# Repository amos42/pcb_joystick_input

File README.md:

# Arcade Joystick 입력 장치

---

[74HC165를 사용한 Arcade Joystick 입력 보드 (DIP. 1P Ver.)](joystick_74hc165_input_1p/)
([README.md](joystick_74hc165_input_1p/README.md))

---

[74HC165를 사용한 Arcade Joystick 입력 보드 (DIP. 2P Ver.)](joystick_74hc165_input/)
([README.md](joystick_74hc165_input/README.md))

---

[74HC165를 사용한 Arcade Joystick 입력 보드 (SMD. 2P Ver.)](joystick_74hc165_input_smd/)
([README.md](joystick_74hc165_input_smd/README.md))

---

[74HC165를 사용한 Arcade Joystick 입력 보드 (JST 커넥터. 2P Ver)](joystick_74hc165_input_jst/)
([README.md](joystick_74hc165_input_jst/README.md))

---

[Raspberry Pie GPIO 입력 모듈](joystick_gpio_input/)
([README.md](joystick_gpio_input/README.md))

---

[Arcade 입력 패널 Support 보드](arcade_input_panel_support/)
([README.md](arcade_input_panel_support/README.md))

---

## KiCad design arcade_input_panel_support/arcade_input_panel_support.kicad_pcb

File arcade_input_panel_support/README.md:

# Arcade Input Panel Support Board

다음과 같은 수치에 맞춰 제작 된 입력 패널에서만 사용이 가능하다.

혹은 [도면 파일](input_panel.svg)을 받아서 종이에 프린트하여 나무판에 붙이고 직접 홀쏘로 구멍을 뚫어 사용해도 된다.

### 회로도

### PCB

### PCB 샘플 이미지

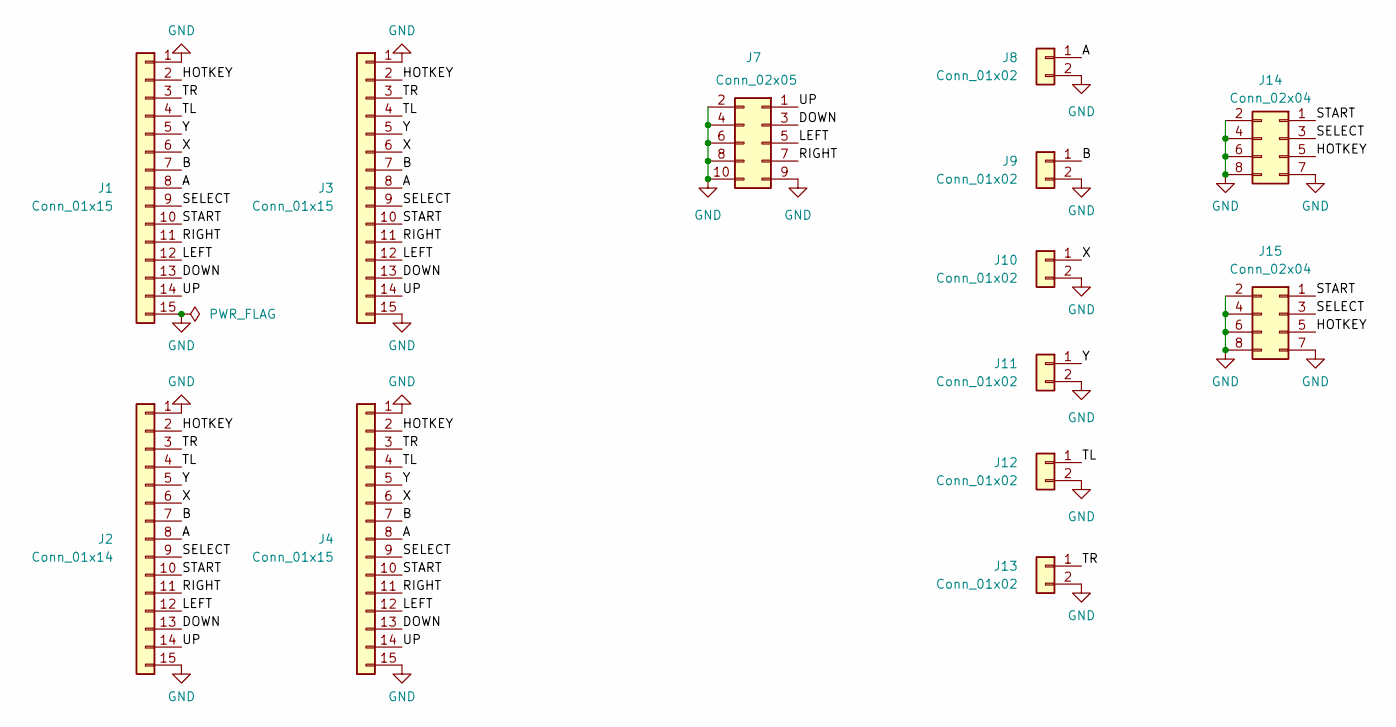
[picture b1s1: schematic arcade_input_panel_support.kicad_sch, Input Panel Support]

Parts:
J1: Conn_01x15; Molex_PicoBlade_53047-1510_1x15_P1.25mm_Vertical
J2: Conn_01x14; Molex_PicoBlade_53047-1510_1x15_P1.25mm_Vertical
J3, J4: Conn_01x15; PinHeader_1x15_P2.54mm_Vertical
J7: Conn_02x05; PinHeader_2x05_P2.54mm_Vertical
J8, J9, J10, J11, J12, J13: Conn_01x02; PinHeader_1x02_P2.54mm_Vertical
J14, J15: Conn_02x04; PinHeader_2x04_P2.54mm_Vertical

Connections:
/A: J1.8, J2.8, J3.8, J4.8, J8.1
/B: J1.7, J2.7, J3.7, J4.7, J9.1
/DOWN: J1.13, J2.13, J3.13, J4.13, J7.3
/HOTKEY: J1.2, J2.2, J3.2, J4.2, J14.5, J15.5
/LEFT: J1.12, J2.12, J3.12, J4.12, J7.5
/RIGHT: J1.11, J2.11, J3.11, J4.11, J7.7
/SELECT: J1.9, J2.9, J3.9, J4.9, J14.3, J15.3
/START: J1.10, J2.10, J3.10, J4.10, J14.1, J15.1
/TL: J1.4, J2.4, J3.4, J4.4, J12.1
/TR: J1.3, J2.3, J3.3, J4.3, J13.1
/UP: J1.14, J2.14, J3.14, J4.14, J7.1
/X: J1.6, J2.6, J3.6, J4.6, J10.1
/Y: J1.5, J2.5, J3.5, J4.5, J11.1
GND: J1.1, J1.15, J2.1, J2.15, J3.1, J3.15, J4.1, J4.15, J7.2, J7.4, J7.6, J7.8, J7.9, J7.10, J8.2, J9.2, J10.2, J11.2, J12.2, J13.2, J14.2, J14.4, J14.6, J14.7, J14.8, J15.2, J15.4, J15.6, J15.7, J15.8

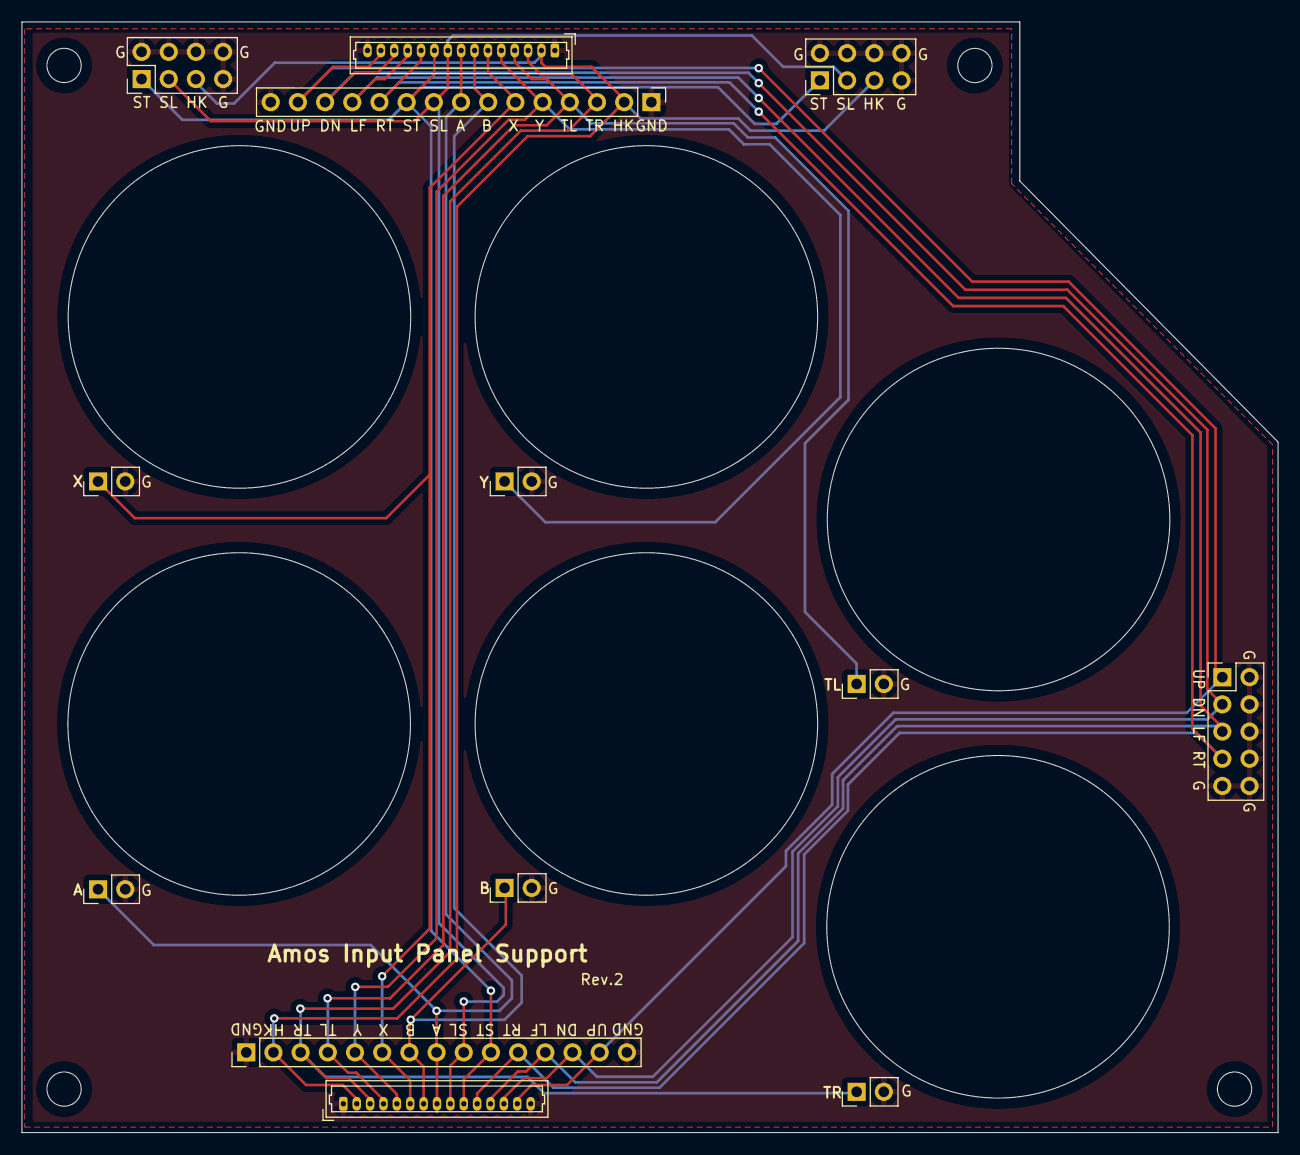
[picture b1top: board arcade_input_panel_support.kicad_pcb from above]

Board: 2 copper layers, 117.3 x 103.8 mm, 13 parts (0 on the bottom side), 14 nets.

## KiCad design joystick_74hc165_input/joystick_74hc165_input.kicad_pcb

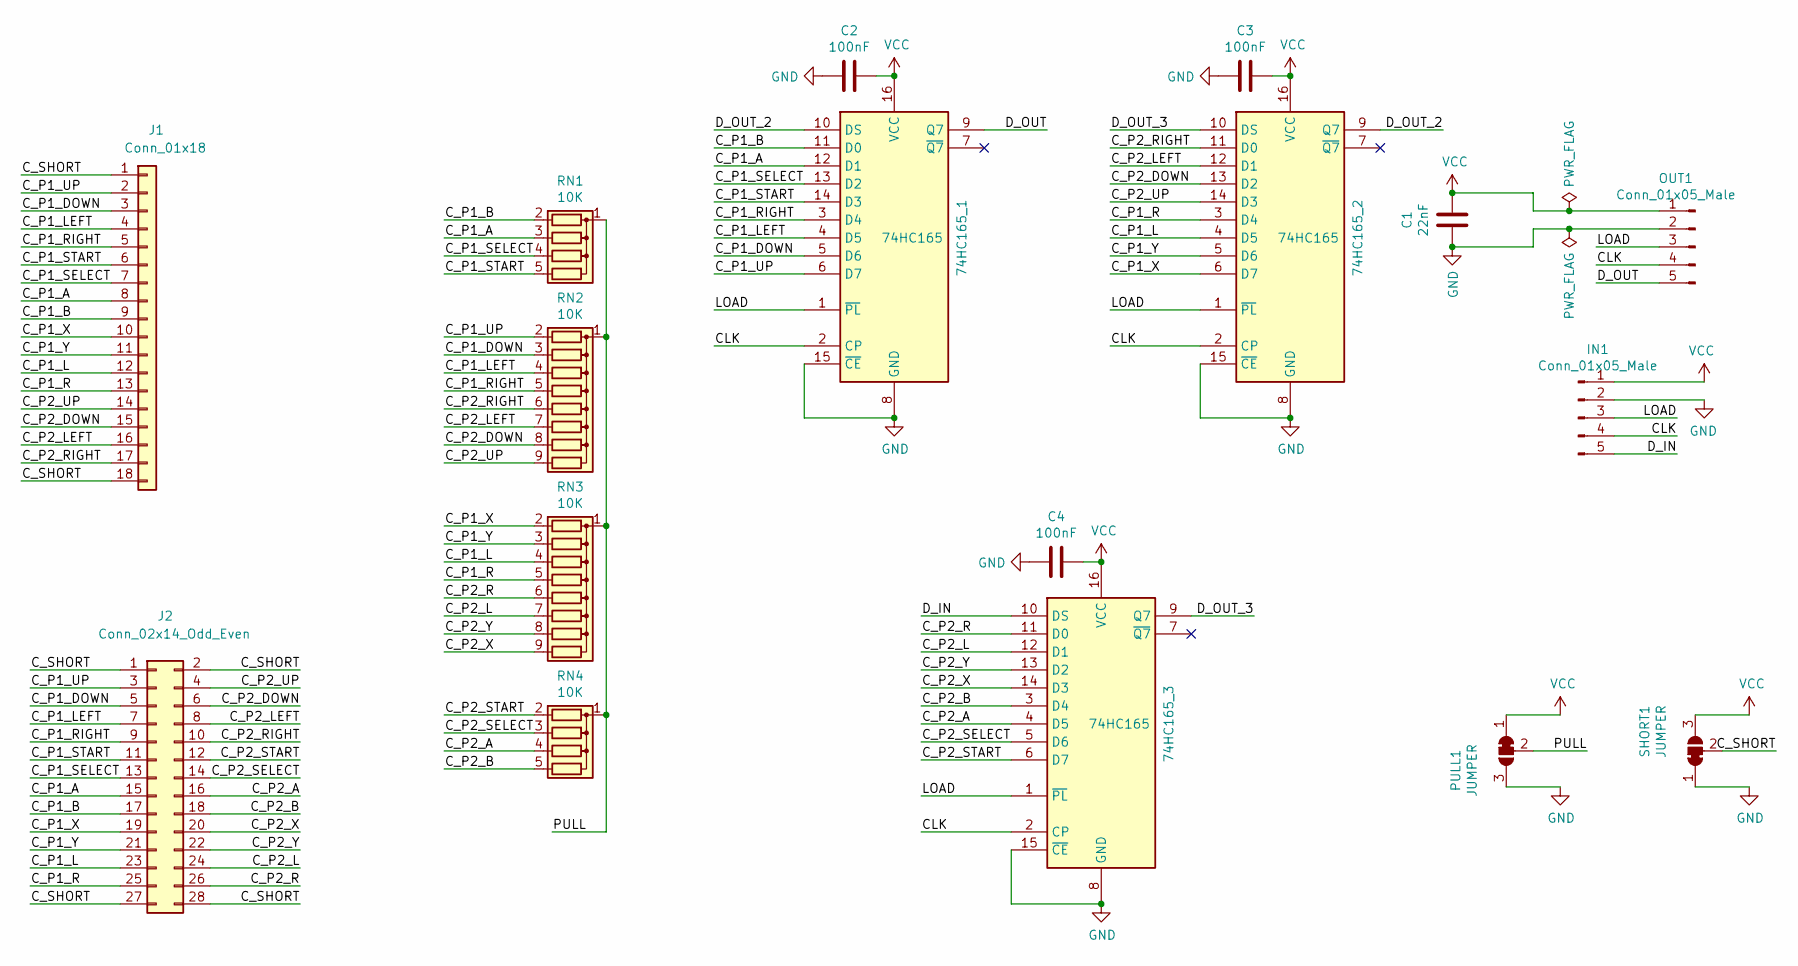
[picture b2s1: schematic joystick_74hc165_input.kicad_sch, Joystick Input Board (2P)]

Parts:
74HC165_1, 74HC165_2, 74HC165_3: 74HC165; DIP-16_W7.62mm
C1: 22nF; C_0805_2012Metric_Pad1.18x1.45mm_HandSolder
C2, C3, C4: 100nF; C_0805_2012Metric_Pad1.18x1.45mm_HandSolder
IN1: Conn_01x05_Male; PinHeader_1x05_P2.54mm_Vertical
J1: Conn_01x18; PinHeader_1x18_P2.54mm_Vertical
J2: Conn_02x14_Odd_Even; PinHeader_2x14_P2.54mm_Vertical
OUT1: Conn_01x05_Male; PinHeader_1x05_P2.54mm_Vertical
PULL1: JUMPER; SolderJumper-3_P1.3mm_Bridged12_Pad1.0x1.5mm_NumberLabels
RN1, RN4: 10K; R_Array_SIP5
RN2, RN3: 10K; R_Array_SIP9
SHORT1: JUMPER; SolderJumper-3_P1.3mm_Bridged12_Pad1.0x1.5mm_NumberLabels

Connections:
/CLK: 74HC165_1.2 (CP), 74HC165_2.2 (CP), 74HC165_3.2 (CP), IN1.4, OUT1.4
/C_P1_A: 74HC165_1.12 (D1), J1.8, J2.15, RN1.3 (R2)
/C_P1_B: 74HC165_1.11 (D0), J1.9, J2.17, RN1.2 (R1)
/C_P1_DOWN: 74HC165_1.5 (D6), J1.3, J2.5, RN2.3 (R2)
/C_P1_L: 74HC165_2.4 (D5), J1.12, J2.23, RN3.4 (R3)
/C_P1_LEFT: 74HC165_1.4 (D5), J1.4, J2.7, RN2.4 (R3)
/C_P1_R: 74HC165_2.3 (D4), J1.13, J2.25, RN3.5 (R4)
/C_P1_RIGHT: 74HC165_1.3 (D4), J1.5, J2.9, RN2.5 (R4)
/C_P1_SELECT: 74HC165_1.13 (D2), J1.7, J2.13, RN1.4 (R3)
/C_P1_START: 74HC165_1.14 (D3), J1.6, J2.11, RN1.5 (R4)
/C_P1_UP: 74HC165_1.6 (D7), J1.2, J2.3, RN2.2 (R1)
/C_P1_X: 74HC165_2.6 (D7), J1.10, J2.19, RN3.2 (R1)
/C_P1_Y: 74HC165_2.5 (D6), J1.11, J2.21, RN3.3 (R2)
/C_P2_A: 74HC165_3.4 (D5), J2.16, RN4.4 (R3)
/C_P2_B: 74HC165_3.3 (D4), J2.18, RN4.5 (R4)
/C_P2_DOWN: 74HC165_2.13 (D2), J1.15, J2.6, RN2.8 (R7)
/C_P2_L: 74HC165_3.12 (D1), J2.24, RN3.7 (R6)
/C_P2_LEFT: 74HC165_2.12 (D1), J1.16, J2.8, RN2.7 (R6)
/C_P2_R: 74HC165_3.11 (D0), J2.26, RN3.6 (R5)
/C_P2_RIGHT: 74HC165_2.11 (D0), J1.17, J2.10, RN2.6 (R5)
/C_P2_SELECT: 74HC165_3.5 (D6), J2.14, RN4.3 (R2)
/C_P2_START: 74HC165_3.6 (D7), J2.12, RN4.2 (R1)
/C_P2_UP: 74HC165_2.14 (D3), J1.14, J2.4, RN2.9 (R8)
/C_P2_X: 74HC165_3.14 (D3), J2.20, RN3.9 (R8)
/C_P2_Y: 74HC165_3.13 (D2), J2.22, RN3.8 (R7)
/C_SHORT: J1.1, J1.18, J2.1, J2.2, J2.27, J2.28, SHORT1.2 (C)
/D_IN: 74HC165_3.10 (DS), IN1.5
/D_OUT: 74HC165_1.9 (Q7), OUT1.5
/D_OUT_2: 74HC165_1.10 (DS), 74HC165_2.9 (Q7)
/D_OUT_3: 74HC165_2.10 (DS), 74HC165_3.9 (Q7)
/LOAD: 74HC165_1.1 (~PL), 74HC165_2.1 (~PL), 74HC165_3.1 (~PL), IN1.3, OUT1.3
/PULL: PULL1.2 (C), RN1.1 (common), RN2.1 (common), RN3.1 (common), RN4.1 (common)
GND: 74HC165_1.8 (GND), 74HC165_1.15 (~CE), 74HC165_2.8 (GND), 74HC165_2.15 (~CE), 74HC165_3.8 (GND), 74HC165_3.15 (~CE), C1.2, C2.2, C3.2, C4.2, IN1.2, OUT1.2, PULL1.3 (B), SHORT1.1 (A)
VCC: 74HC165_1.16 (VCC), 74HC165_2.16 (VCC), 74HC165_3.16 (VCC), C1.1, C2.1, C3.1, C4.1, IN1.1, OUT1.1, PULL1.1 (A), SHORT1.3 (B)

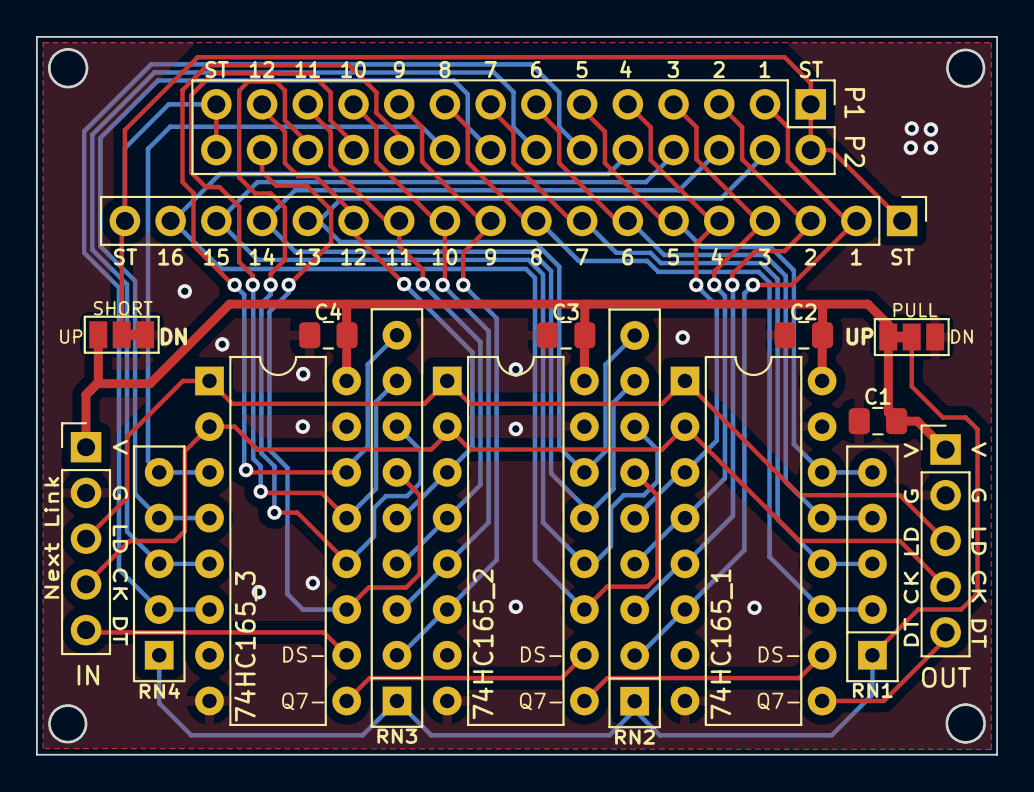
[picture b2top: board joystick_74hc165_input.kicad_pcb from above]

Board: 2 copper layers, 53.3 x 39.9 mm, 17 parts (0 on the bottom side), 34 nets.

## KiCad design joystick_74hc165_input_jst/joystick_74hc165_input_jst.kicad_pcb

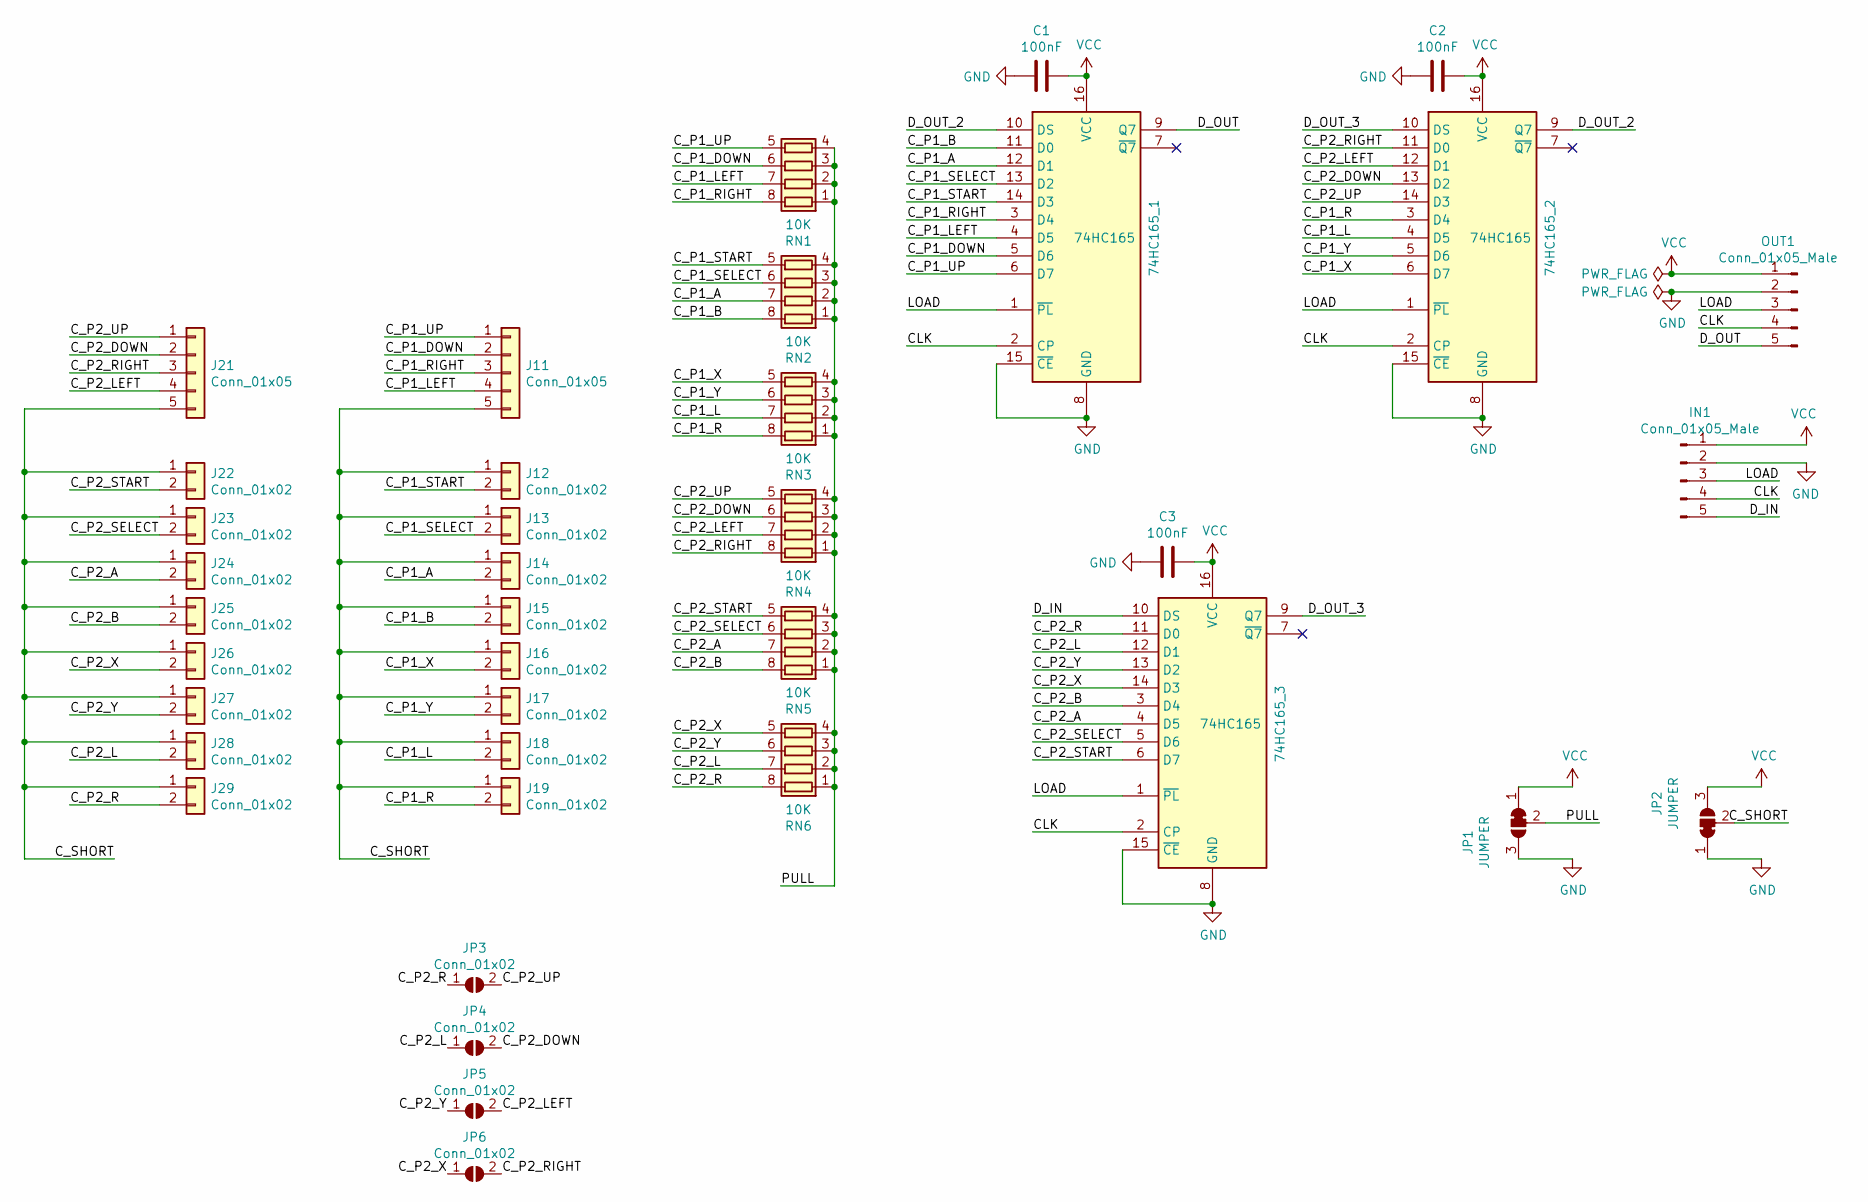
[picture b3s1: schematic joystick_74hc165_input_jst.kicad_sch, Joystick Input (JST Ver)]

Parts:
74HC165_1, 74HC165_2, 74HC165_3: 74HC165; SOIC-16_3.9x9.9mm_P1.27mm
C1, C2, C3: 100nF; C_0805_2012Metric_Pad1.18x1.45mm_HandSolder
IN1: Conn_01x05_Male; PinHeader_1x05_P2.54mm_Vertical
J11, J21: Conn_01x05; JST_XH_B5B-XH-A_1x05_P2.50mm_Vertical
J12, J13, J14, J15, J16, J17, J18, J19, J22, J23, J24, J25, J26, J27, J28, J29: Conn_01x02; JST_XH_B2B-XH-A_1x02_P2.50mm_Vertical
JP1, JP2: JUMPER; SolderJumper-3_P1.3mm_Bridged12_Pad1.0x1.5mm_NumberLabels
JP3, JP4, JP5, JP6: Conn_01x02; SolderJumper-2_P1.3mm_Bridged_RoundedPad1.0x1.5mm
OUT1: Conn_01x05_Male; PinHeader_1x05_P2.54mm_Vertical
RN1, RN2, RN3, RN4, RN5, RN6: 10K; R_Array_Concave_4x0603

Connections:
/CLK: 74HC165_1.2 (CP), 74HC165_2.2 (CP), 74HC165_3.2 (CP), IN1.4, OUT1.4
/C_P1_A: 74HC165_1.12 (D1), J14.2, RN2.7 (R2.2)
/C_P1_B: 74HC165_1.11 (D0), J15.2, RN2.8 (R1.2)
/C_P1_DOWN: 74HC165_1.5 (D6), J11.2, RN1.6 (R3.2)
/C_P1_L: 74HC165_2.4 (D5), J18.2, RN3.7 (R2.2)
/C_P1_LEFT: 74HC165_1.4 (D5), J11.4, RN1.7 (R2.2)
/C_P1_R: 74HC165_2.3 (D4), J19.2, RN3.8 (R1.2)
/C_P1_RIGHT: 74HC165_1.3 (D4), J11.3, RN1.8 (R1.2)
/C_P1_SELECT: 74HC165_1.13 (D2), J13.2, RN2.6 (R3.2)
/C_P1_START: 74HC165_1.14 (D3), J12.2, RN2.5 (R4.2)
/C_P1_UP: 74HC165_1.6 (D7), J11.1, RN1.5 (R4.2)
/C_P1_X: 74HC165_2.6 (D7), J16.2, RN3.5 (R4.2)
/C_P1_Y: 74HC165_2.5 (D6), J17.2, RN3.6 (R3.2)
/C_P2_A: 74HC165_3.4 (D5), J24.2, RN5.7 (R2.2)
/C_P2_B: 74HC165_3.3 (D4), J25.2, RN5.8 (R1.2)
/C_P2_DOWN: 74HC165_2.13 (D2), J21.2, JP4.2 (B), RN4.6 (R3.2)
/C_P2_L: 74HC165_3.12 (D1), J28.2, JP4.1 (A), RN6.7 (R2.2)
/C_P2_LEFT: 74HC165_2.12 (D1), J21.4, JP5.2 (B), RN4.7 (R2.2)
/C_P2_R: 74HC165_3.11 (D0), J29.2, JP3.1 (A), RN6.8 (R1.2)
/C_P2_RIGHT: 74HC165_2.11 (D0), J21.3, JP6.2 (B), RN4.8 (R1.2)
/C_P2_SELECT: 74HC165_3.5 (D6), J23.2, RN5.6 (R3.2)
/C_P2_START: 74HC165_3.6 (D7), J22.2, RN5.5 (R4.2)
/C_P2_UP: 74HC165_2.14 (D3), J21.1, JP3.2 (B), RN4.5 (R4.2)
/C_P2_X: 74HC165_3.14 (D3), J26.2, JP6.1 (A), RN6.5 (R4.2)
/C_P2_Y: 74HC165_3.13 (D2), J27.2, JP5.1 (A), RN6.6 (R3.2)
/C_SHORT: J11.5, J12.1, J13.1, J14.1, J15.1, J16.1, J17.1, J18.1, J19.1, J21.5, J22.1, J23.1, J24.1, J25.1, J26.1, J27.1, J28.1, J29.1, JP2.2 (C)
/D_IN: 74HC165_3.10 (DS), IN1.5
/D_OUT: 74HC165_1.9 (Q7), OUT1.5
/D_OUT_2: 74HC165_1.10 (DS), 74HC165_2.9 (Q7)
/D_OUT_3: 74HC165_2.10 (DS), 74HC165_3.9 (Q7)
/LOAD: 74HC165_1.1 (~PL), 74HC165_2.1 (~PL), 74HC165_3.1 (~PL), IN1.3, OUT1.3
/PULL: JP1.2 (C), RN1.1 (R1.1), RN1.2 (R2.1), RN1.3 (R3.1), RN1.4 (R4.1), RN2.1 (R1.1), RN2.2 (R2.1), RN2.3 (R3.1), RN2.4 (R4.1), RN3.1 (R1.1), RN3.2 (R2.1), RN3.3 (R3.1), RN3.4 (R4.1), RN4.1 (R1.1), RN4.2 (R2.1), RN4.3 (R3.1), RN4.4 (R4.1), RN5.1 (R1.1), RN5.2 (R2.1), RN5.3 (R3.1), RN5.4 (R4.1), RN6.1 (R1.1), RN6.2 (R2.1), RN6.3 (R3.1), RN6.4 (R4.1)
GND: 74HC165_1.8 (GND), 74HC165_1.15 (~CE), 74HC165_2.8 (GND), 74HC165_2.15 (~CE), 74HC165_3.8 (GND), 74HC165_3.15 (~CE), C1.2, C2.2, C3.2, IN1.2, JP1.3 (B), JP2.1 (A), OUT1.2
VCC: 74HC165_1.16 (VCC), 74HC165_2.16 (VCC), 74HC165_3.16 (VCC), C1.1, C2.1, C3.1, IN1.1, JP1.1 (A), JP2.3 (B), OUT1.1

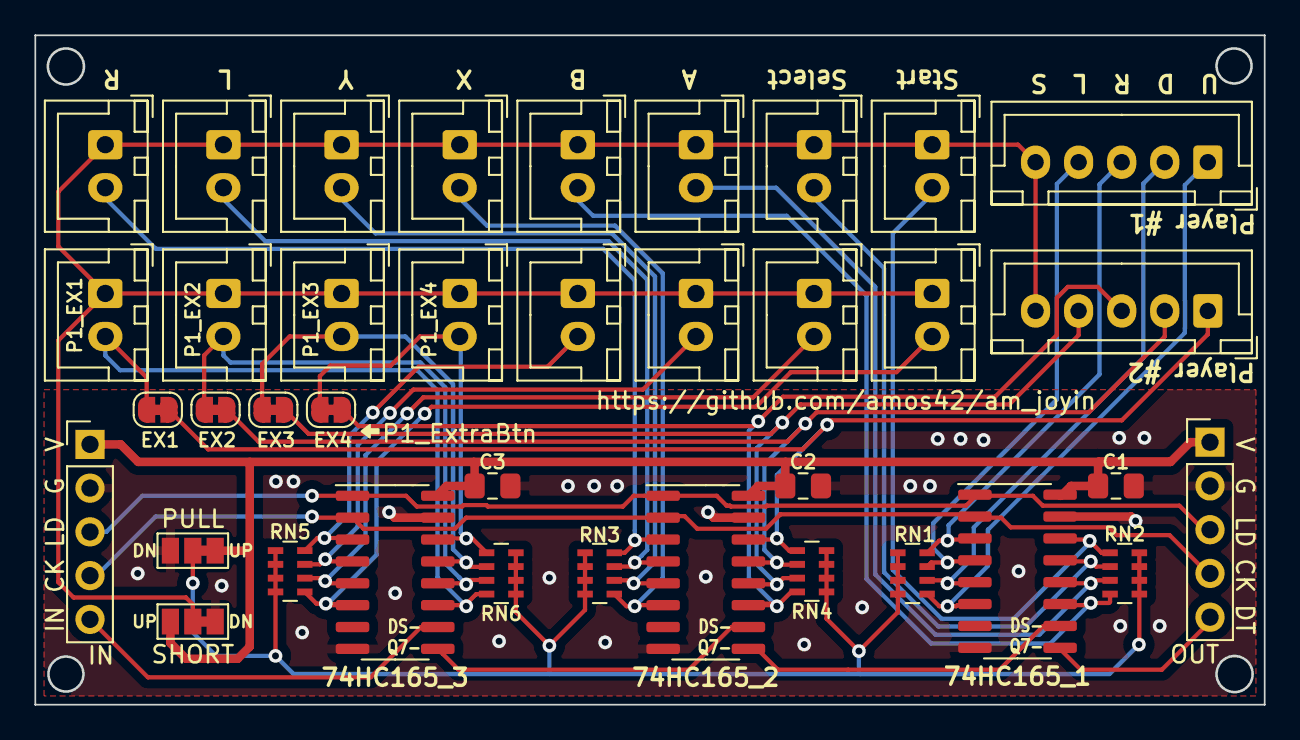
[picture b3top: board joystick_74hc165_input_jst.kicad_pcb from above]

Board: 2 copper layers, 71.4 x 38.9 mm, 38 parts (0 on the bottom side), 34 nets.

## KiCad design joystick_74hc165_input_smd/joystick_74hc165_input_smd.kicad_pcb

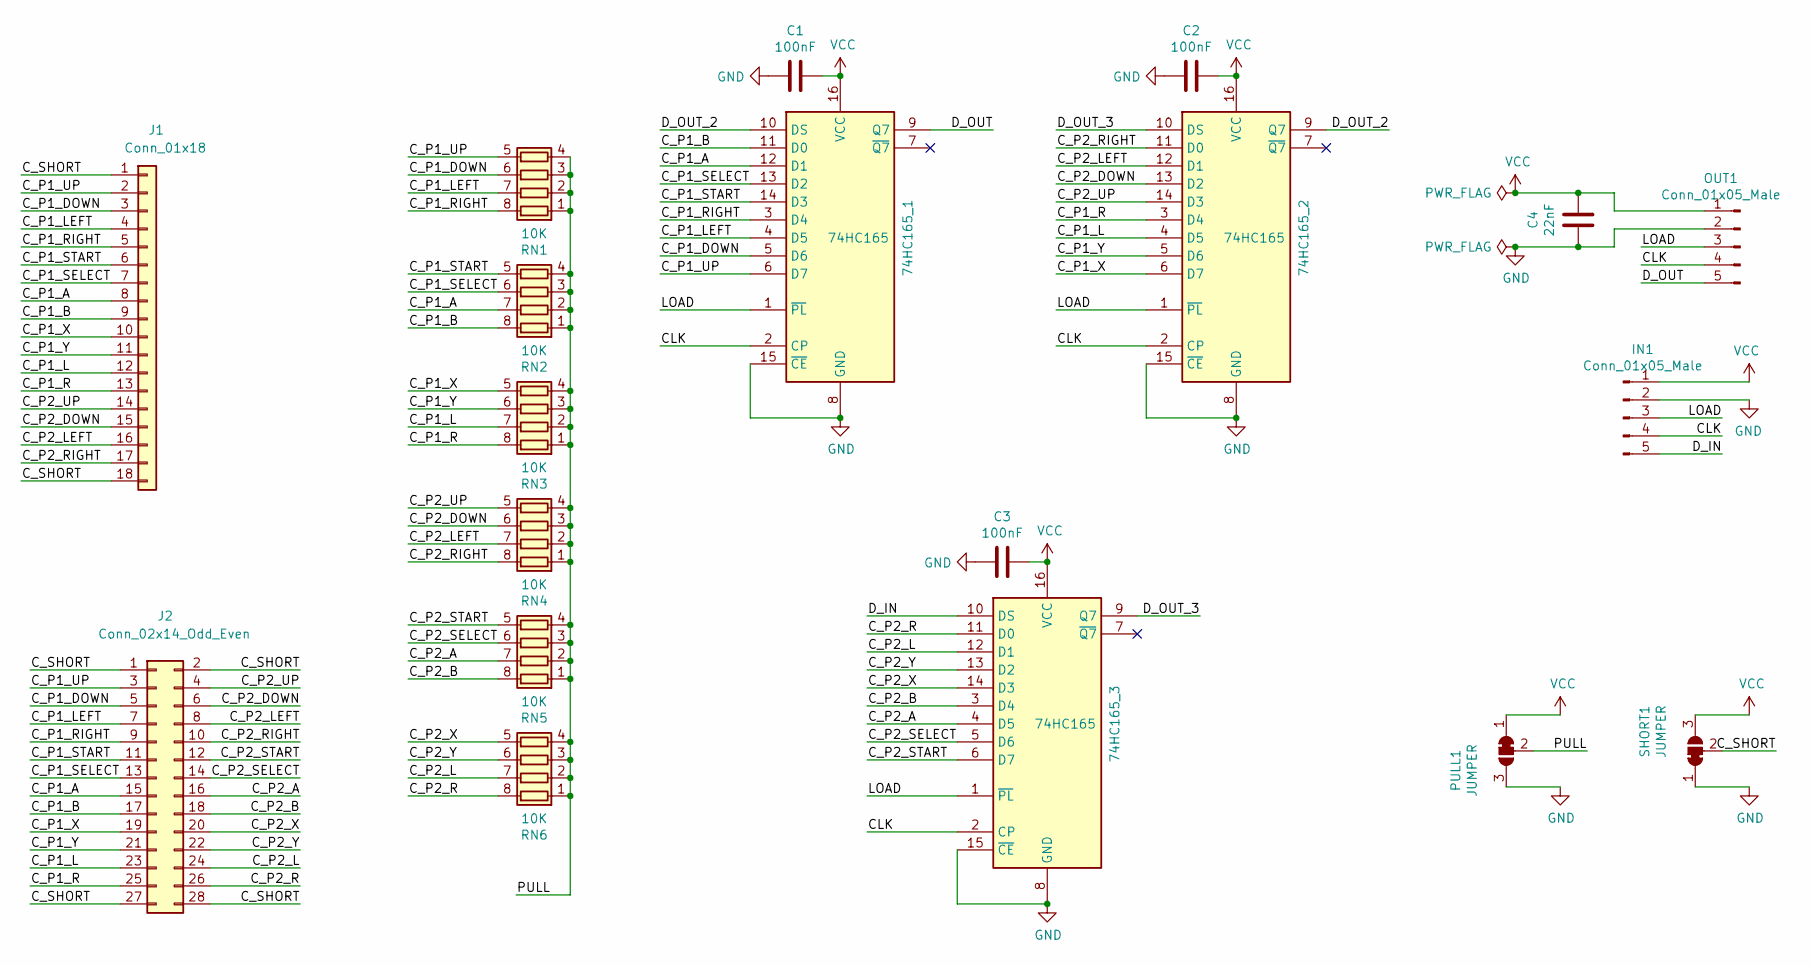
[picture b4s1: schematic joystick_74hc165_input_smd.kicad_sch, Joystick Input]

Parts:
74HC165_1, 74HC165_2, 74HC165_3: 74HC165; SOIC-16_3.9x9.9mm_P1.27mm
C1, C2, C3: 100nF; C_0805_2012Metric_Pad1.18x1.45mm_HandSolder
C4: 22nF; C_0805_2012Metric_Pad1.18x1.45mm_HandSolder
IN1: Conn_01x05_Male; PinHeader_1x05_P2.54mm_Vertical
J1: Conn_01x18; PinHeader_1x18_P2.54mm_Vertical
J2: Conn_02x14_Odd_Even; PinHeader_2x14_P2.54mm_Vertical
OUT1: Conn_01x05_Male; PinHeader_1x05_P2.54mm_Vertical
PULL1: JUMPER; SolderJumper-3_P1.3mm_Bridged12_Pad1.0x1.5mm_NumberLabels
RN1, RN2, RN3, RN4, RN5, RN6: 10K; R_Array_Concave_4x0603
SHORT1: JUMPER; SolderJumper-3_P1.3mm_Bridged12_Pad1.0x1.5mm_NumberLabels

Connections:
/CLK: 74HC165_1.2 (CP), 74HC165_2.2 (CP), 74HC165_3.2 (CP), IN1.4, OUT1.4
/C_P1_A: 74HC165_1.12 (D1), J1.8, J2.15, RN2.7 (R2.2)
/C_P1_B: 74HC165_1.11 (D0), J1.9, J2.17, RN2.8 (R1.2)
/C_P1_DOWN: 74HC165_1.5 (D6), J1.3, J2.5, RN1.6 (R3.2)
/C_P1_L: 74HC165_2.4 (D5), J1.12, J2.23, RN3.7 (R2.2)
/C_P1_LEFT: 74HC165_1.4 (D5), J1.4, J2.7, RN1.7 (R2.2)
/C_P1_R: 74HC165_2.3 (D4), J1.13, J2.25, RN3.8 (R1.2)
/C_P1_RIGHT: 74HC165_1.3 (D4), J1.5, J2.9, RN1.8 (R1.2)
/C_P1_SELECT: 74HC165_1.13 (D2), J1.7, J2.13, RN2.6 (R3.2)
/C_P1_START: 74HC165_1.14 (D3), J1.6, J2.11, RN2.5 (R4.2)
/C_P1_UP: 74HC165_1.6 (D7), J1.2, J2.3, RN1.5 (R4.2)
/C_P1_X: 74HC165_2.6 (D7), J1.10, J2.19, RN3.5 (R4.2)
/C_P1_Y: 74HC165_2.5 (D6), J1.11, J2.21, RN3.6 (R3.2)
/C_P2_A: 74HC165_3.4 (D5), J2.16, RN5.7 (R2.2)
/C_P2_B: 74HC165_3.3 (D4), J2.18, RN5.8 (R1.2)
/C_P2_DOWN: 74HC165_2.13 (D2), J1.15, J2.6, RN4.6 (R3.2)
/C_P2_L: 74HC165_3.12 (D1), J2.24, RN6.7 (R2.2)
/C_P2_LEFT: 74HC165_2.12 (D1), J1.16, J2.8, RN4.7 (R2.2)
/C_P2_R: 74HC165_3.11 (D0), J2.26, RN6.8 (R1.2)
/C_P2_RIGHT: 74HC165_2.11 (D0), J1.17, J2.10, RN4.8 (R1.2)
/C_P2_SELECT: 74HC165_3.5 (D6), J2.14, RN5.6 (R3.2)
/C_P2_START: 74HC165_3.6 (D7), J2.12, RN5.5 (R4.2)
/C_P2_UP: 74HC165_2.14 (D3), J1.14, J2.4, RN4.5 (R4.2)
/C_P2_X: 74HC165_3.14 (D3), J2.20, RN6.5 (R4.2)
/C_P2_Y: 74HC165_3.13 (D2), J2.22, RN6.6 (R3.2)
/C_SHORT: J1.1, J1.18, J2.1, J2.2, J2.27, J2.28, SHORT1.2 (C)
/D_IN: 74HC165_3.10 (DS), IN1.5
/D_OUT: 74HC165_1.9 (Q7), OUT1.5
/D_OUT_2: 74HC165_1.10 (DS), 74HC165_2.9 (Q7)
/D_OUT_3: 74HC165_2.10 (DS), 74HC165_3.9 (Q7)
/LOAD: 74HC165_1.1 (~PL), 74HC165_2.1 (~PL), 74HC165_3.1 (~PL), IN1.3, OUT1.3
/PULL: PULL1.2 (C), RN1.1 (R1.1), RN1.2 (R2.1), RN1.3 (R3.1), RN1.4 (R4.1), RN2.1 (R1.1), RN2.2 (R2.1), RN2.3 (R3.1), RN2.4 (R4.1), RN3.1 (R1.1), RN3.2 (R2.1), RN3.3 (R3.1), RN3.4 (R4.1), RN4.1 (R1.1), RN4.2 (R2.1), RN4.3 (R3.1), RN4.4 (R4.1), RN5.1 (R1.1), RN5.2 (R2.1), RN5.3 (R3.1), RN5.4 (R4.1), RN6.1 (R1.1), RN6.2 (R2.1), RN6.3 (R3.1), RN6.4 (R4.1)
GND: 74HC165_1.8 (GND), 74HC165_1.15 (~CE), 74HC165_2.8 (GND), 74HC165_2.15 (~CE), 74HC165_3.8 (GND), 74HC165_3.15 (~CE), C1.2, C2.2, C3.2, C4.2, IN1.2, OUT1.2, PULL1.3 (B), SHORT1.1 (A)
VCC: 74HC165_1.16 (VCC), 74HC165_2.16 (VCC), 74HC165_3.16 (VCC), C1.1, C2.1, C3.1, C4.1, IN1.1, OUT1.1, PULL1.1 (A), SHORT1.3 (B)

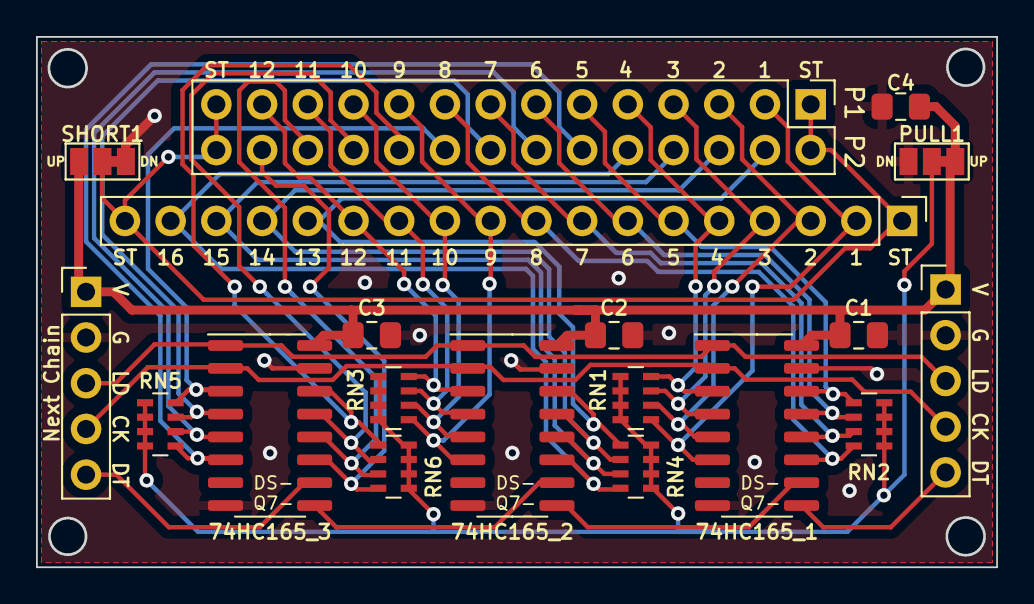
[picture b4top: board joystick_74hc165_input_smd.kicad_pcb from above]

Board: 2 copper layers, 53.3 x 29.5 mm, 19 parts (0 on the bottom side), 34 nets.

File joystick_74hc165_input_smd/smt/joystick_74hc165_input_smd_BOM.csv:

Designator,Footprint,Comment,
"RN2,RN1,RN4,RN5,RN3,RN6",R_Array_Concave_4x0603,10K,C29718
"C1,C2,C3",C_0805_2012Metric_Pad1.18x1.45mm_HandSolder,100nF,
"74HC165_1,74HC165_2,74HC165_3",SOIC-16_3.9x9.9mm_P1.27mm,74HC165,
C4,C_0805_2012Metric_Pad1.18x1.45mm_HandSolder,22nF,

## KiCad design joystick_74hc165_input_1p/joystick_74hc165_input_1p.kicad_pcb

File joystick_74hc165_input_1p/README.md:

# 74HC165를 이용한 Joystick (1P)입력 보드

회로도

PCB 이미지 앞면

PCB 이미지 뒷면

샘플 이미지

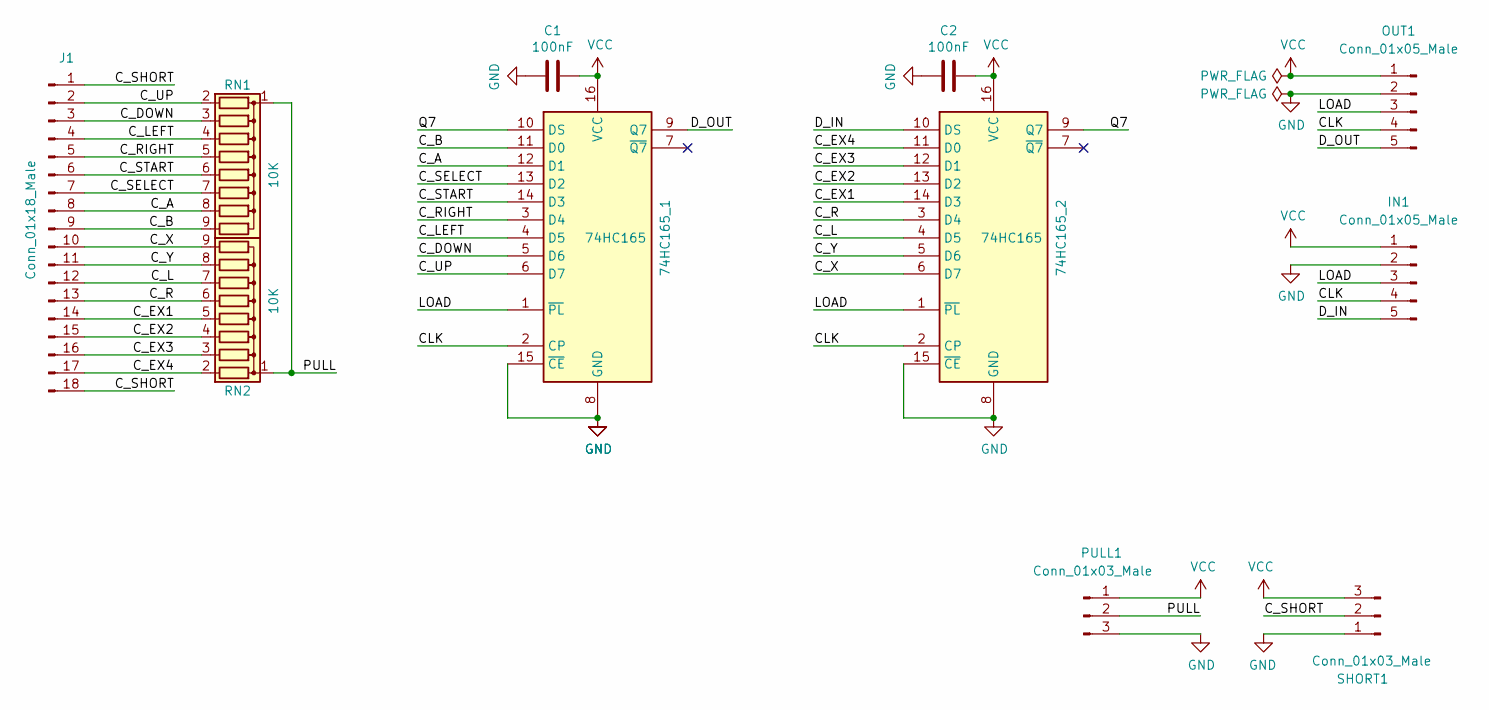
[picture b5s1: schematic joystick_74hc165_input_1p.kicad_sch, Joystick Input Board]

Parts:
74HC165_1, 74HC165_2: 74HC165; DIP-16_W7.62mm
C1, C2: 100nF; C_Disc_D4.3mm_W1.9mm_P5.00mm
IN1: Conn_01x05_Male; PinHeader_1x05_P2.54mm_Vertical
J1: Conn_01x18_Male; PinHeader_1x18_P2.54mm_Vertical
OUT1: Conn_01x05_Male; PinHeader_1x05_P2.54mm_Vertical
PULL1: Conn_01x03_Male; SolderJumper-3_P1.3mm_Bridged12_Pad1.0x1.5mm_NumberLabels
RN1, RN2: 10K; R_Array_SIP9
SHORT1: Conn_01x03_Male; SolderJumper-3_P1.3mm_Bridged12_Pad1.0x1.5mm_NumberLabels

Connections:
/CLK: 74HC165_1.2 (CP), 74HC165_2.2 (CP), IN1.4, OUT1.4
/C_A: 74HC165_1.12 (D1), J1.8, RN1.8 (R7)
/C_B: 74HC165_1.11 (D0), J1.9, RN1.9 (R8)
/C_DOWN: 74HC165_1.5 (D6), J1.3, RN1.3 (R2)
/C_EX1: 74HC165_2.14 (D3), J1.14, RN2.5 (R4)
/C_EX2: 74HC165_2.13 (D2), J1.15, RN2.4 (R3)
/C_EX3: 74HC165_2.12 (D1), J1.16, RN2.3 (R2)
/C_EX4: 74HC165_2.11 (D0), J1.17, RN2.2 (R1)
/C_L: 74HC165_2.4 (D5), J1.12, RN2.7 (R6)
/C_LEFT: 74HC165_1.4 (D5), J1.4, RN1.4 (R3)
/C_R: 74HC165_2.3 (D4), J1.13, RN2.6 (R5)
/C_RIGHT: 74HC165_1.3 (D4), J1.5, RN1.5 (R4)
/C_SELECT: 74HC165_1.13 (D2), J1.7, RN1.7 (R6)
/C_SHORT: J1.1, J1.18, SHORT1.2
/C_START: 74HC165_1.14 (D3), J1.6, RN1.6 (R5)
/C_UP: 74HC165_1.6 (D7), J1.2, RN1.2 (R1)
/C_X: 74HC165_2.6 (D7), J1.10, RN2.9 (R8)
/C_Y: 74HC165_2.5 (D6), J1.11, RN2.8 (R7)
/D_IN: 74HC165_2.10 (DS), IN1.5
/D_OUT: 74HC165_1.9 (Q7), OUT1.5
/LOAD: 74HC165_1.1 (~PL), 74HC165_2.1 (~PL), IN1.3, OUT1.3
/PULL: PULL1.2, RN1.1 (common), RN2.1 (common)
/Q7: 74HC165_1.10 (DS), 74HC165_2.9 (Q7)
GND: 74HC165_1.8 (GND), 74HC165_1.15 (~CE), 74HC165_2.8 (GND), 74HC165_2.15 (~CE), C1.2, C2.2, IN1.2, OUT1.2, PULL1.3, SHORT1.1
VCC: 74HC165_1.16 (VCC), 74HC165_2.16 (VCC), C1.1, C2.1, IN1.1, OUT1.1, PULL1.1, SHORT1.3

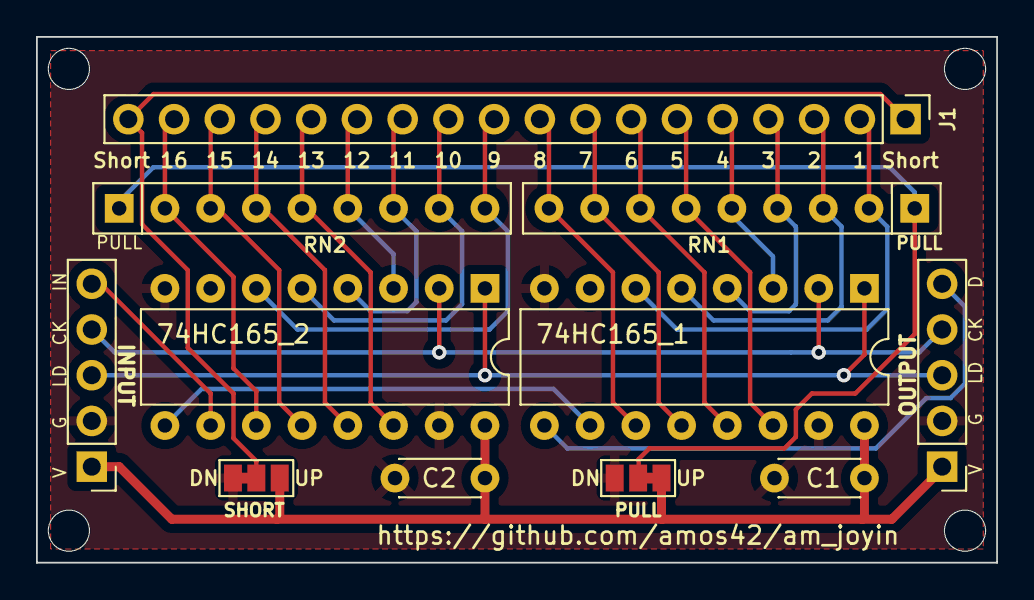
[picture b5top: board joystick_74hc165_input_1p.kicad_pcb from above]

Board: 2 copper layers, 53.3 x 29.2 mm, 11 parts (0 on the bottom side), 25 nets.

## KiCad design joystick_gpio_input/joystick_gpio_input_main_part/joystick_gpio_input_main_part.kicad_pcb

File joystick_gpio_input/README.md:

# Raspberry Pie GPIO 입력 모듈

GPIO 보호 기능을 갖는 입력 모듈

---
am_joyin 혹은 mk_arcade_joystick_rpi의 GPIO 입력 맵을 기본으로 했다.

am_joyin 드라이버도 해당 GPIO 입력 맵과 호환된다.

기본적으로는 1P를 기준으로 했으며, 2P 용으로는 GPIO를 모두 소진한다는 문제 때문에 2P는 optional 하게 추가 지원하도록 했다.

1P의 경우, HK를 GPIO11로 사용하게 했는데, 이를 원활히 사용하려면 am_joyin 드라이버를 쓰면 된다.

> ***info***  
am_joyin 링크 : [https://github.com/amos42/am_joyin](https://github.com/amos42/am_joyin)

## 메인 파트

### 회로도

### PCB

### BOM

| Designator | Package           | Quantity | Designation |
|------------|-------------------|----------|-------------|
| R1~R13     | R_0805_2012Metric | 13       | 6.8K        |

### 샘플 이미지

---

## Raspberry Pi Connector 1P 파트

### 회로도

### PCB

### 샘플 이미지

---

## Raspberry Pi Connector 2p 파트

### 회로도

### PCB

### 샘플 이미지

## 점퍼 세팅

커넥터 중 J3는 일부 핀을 점퍼 세팅으로 변경이 가능하다.

* *R - 1-2 끊고 2-3 쇼트시, J3의 Right 핀이 GND로 쇼트
* *SL - 1-2 끊고 2-3 쇼트시, J3의 Select 핀이 GND로 쇼트
* *HK - 1-2 끊고 2-3 쇼트시, J3의 HotKey 핀이 GND로 쇼트

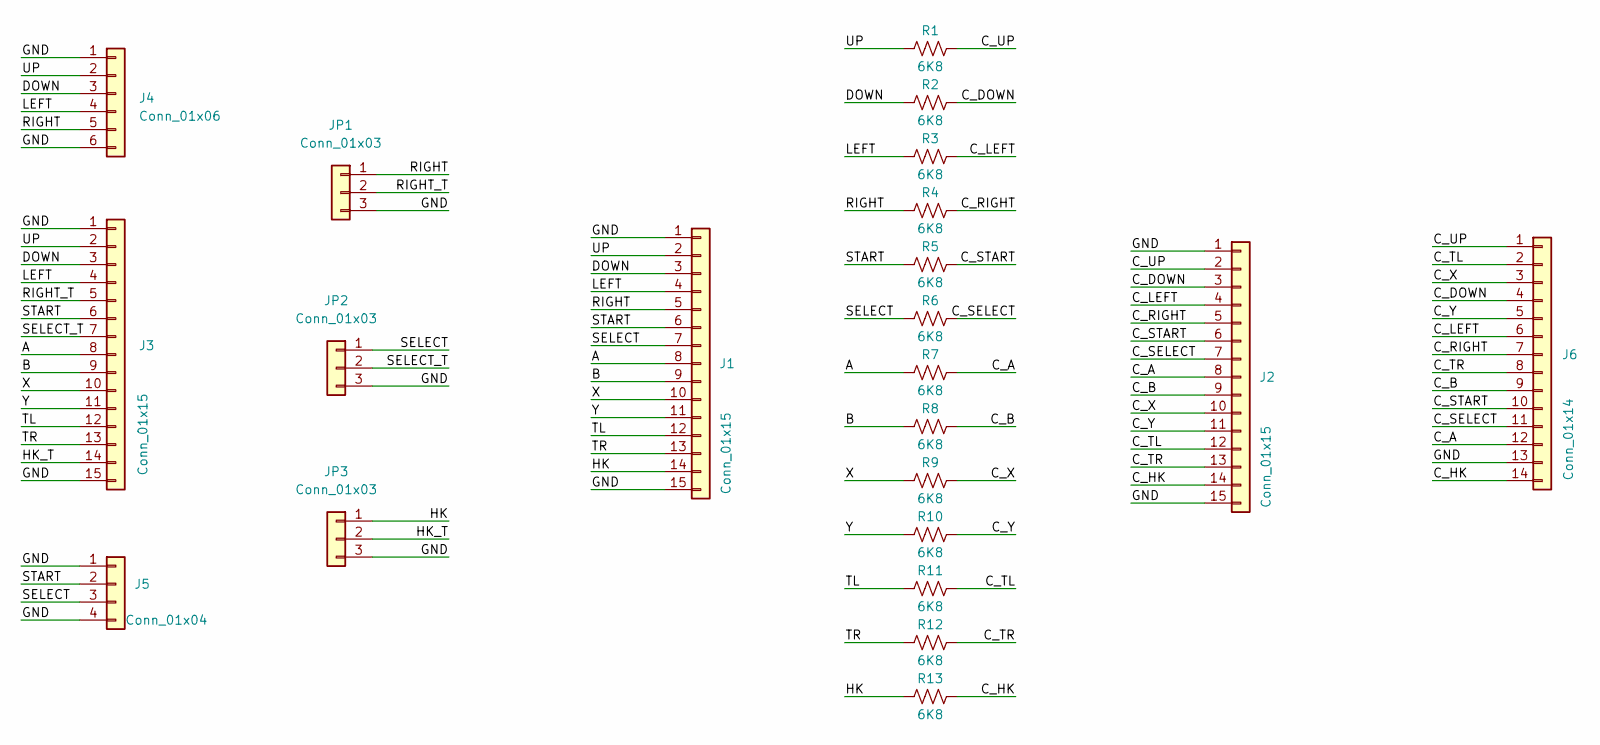
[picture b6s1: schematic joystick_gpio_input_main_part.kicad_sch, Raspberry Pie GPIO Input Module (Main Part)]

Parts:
J1, J2: Conn_01x15; PinHeader_1x15_P2.54mm_Vertical
J3: Conn_01x15; Molex_PicoBlade_53047-1510_1x15_P1.25mm_Vertical
J4: Conn_01x06; Molex_PicoBlade_53047-0610_1x06_P1.25mm_Vertical
J5: Conn_01x04; Molex_PicoBlade_53047-0410_1x04_P1.25mm_Vertical
J6: Conn_01x14; conn_ex_1x14_P1.25mm_Vertical_Left_Labeled
JP1, JP2, JP3: Conn_01x03; PinHeader_1x03_P2.54mm_Vertical
R1, R2, R3, R4, R5, R6, R7, R8, R9, R10, R11, R12, R13: 6K8; R_0805_2012Metric_Pad1.20x1.40mm_HandSolder

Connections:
/A: J1.8, J3.8, R7.1
/B: J1.9, J3.9, R8.1
/C_A: J2.8, J6.12, R7.2
/C_B: J2.9, J6.9, R8.2
/C_DOWN: J2.3, J6.4, R2.2
/C_HK: J2.14, J6.14, R13.2
/C_LEFT: J2.4, J6.6, R3.2
/C_RIGHT: J2.5, J6.7, R4.2
/C_SELECT: J2.7, J6.11, R6.2
/C_START: J2.6, J6.10, R5.2
/C_TL: J2.12, J6.2, R11.2
/C_TR: J2.13, J6.8, R12.2
/C_UP: J2.2, J6.1, R1.2
/C_X: J2.10, J6.3, R9.2
/C_Y: J2.11, J6.5, R10.2
/DOWN: J1.3, J3.3, J4.3, R2.1
/GND: J1.1, J1.15, J2.1, J2.15, J3.1, J3.15, J4.1, J4.6, J5.1, J5.4, J6.13, JP1.3, JP2.3, JP3.3
/HK: J1.14, JP3.1, R13.1
/HK_T: J3.14, JP3.2
/LEFT: J1.4, J3.4, J4.4, R3.1
/RIGHT: J1.5, J4.5, JP1.1, R4.1
/RIGHT_T: J3.5, JP1.2
/SELECT: J1.7, J5.3, JP2.1, R6.1
/SELECT_T: J3.7, JP2.2
/START: J1.6, J3.6, J5.2, R5.1
/TL: J1.12, J3.12, R11.1
/TR: J1.13, J3.13, R12.1
/UP: J1.2, J3.2, J4.2, R1.1
/X: J1.10, J3.10, R9.1
/Y: J1.11, J3.11, R10.1
